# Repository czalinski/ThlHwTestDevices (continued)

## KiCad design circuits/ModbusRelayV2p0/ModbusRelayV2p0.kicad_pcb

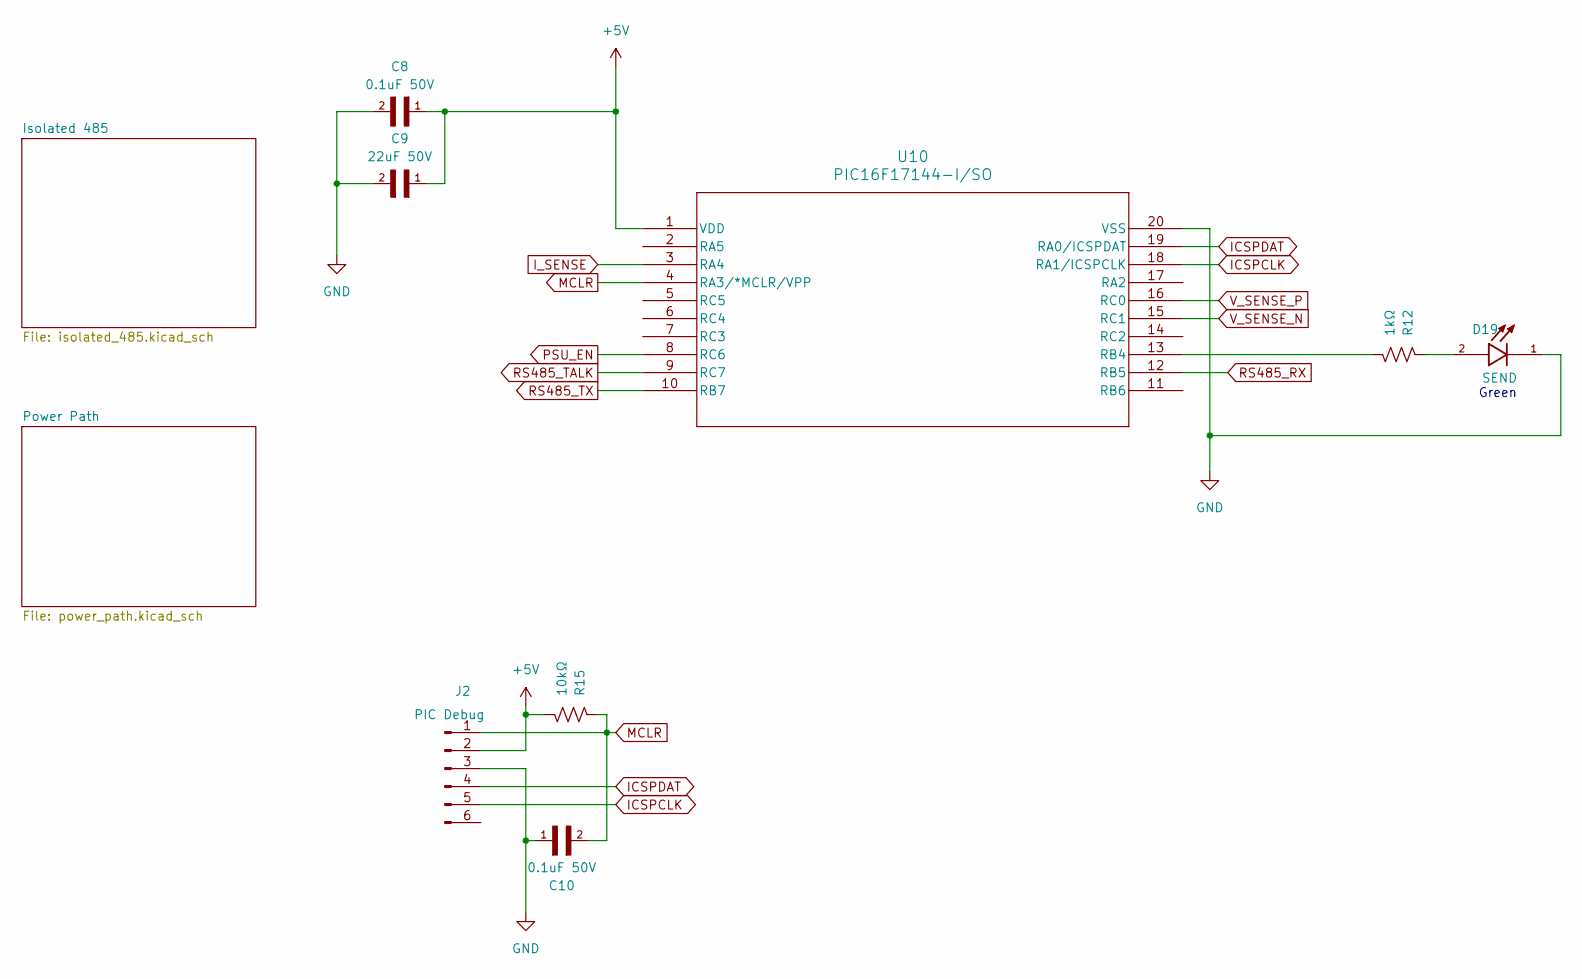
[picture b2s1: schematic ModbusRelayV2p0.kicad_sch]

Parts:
C8, C10: 0.1uF 50V; CAPC2012X70
C9: 22uF 50V; CAPC3216X180N
D19: SEND; LED_LTST-C170GKT; PARTREV I
J2: PIC Debug; PinHeader_1x06_P2.54mm_Horizontal
R12: 1kΩ; RES_1206
R15: 10kΩ; RES_1206
U10: PIC16F17144-I/SO; SOIC20_SO_MCH

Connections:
+5V: C8.1, C9.1, J2.2, R15.2, U10.1 (VDD); also elsewhere on the board
GND: C8.2, C9.2, C10.1, D19.1, J2.3, U10.20 (VSS); also elsewhere on the board
ICSPCLK: J2.5, U10.18 (RA1/ICSPCLK)
ICSPDAT: J2.4, U10.19 (RA0/ICSPDAT)
I_SENSE: U10.3 (RA4); also elsewhere on the board
MCLR: C10.2, J2.1, R15.1, U10.4 (RA3/*MCLR/VPP)
unnamed: D19.2, R12.1
unnamed: R12.2, U10.13 (RB4)
PSU_EN: U10.8 (RC6); also elsewhere on the board
RS485_RX: U10.12 (RB5); also elsewhere on the board
RS485_TALK: U10.9 (RC7); also elsewhere on the board
RS485_TX: U10.10 (RB7); also elsewhere on the board
V_SENSE_N: U10.15 (RC1); also elsewhere on the board
V_SENSE_P: U10.16 (RC0); also elsewhere on the board

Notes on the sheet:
Green

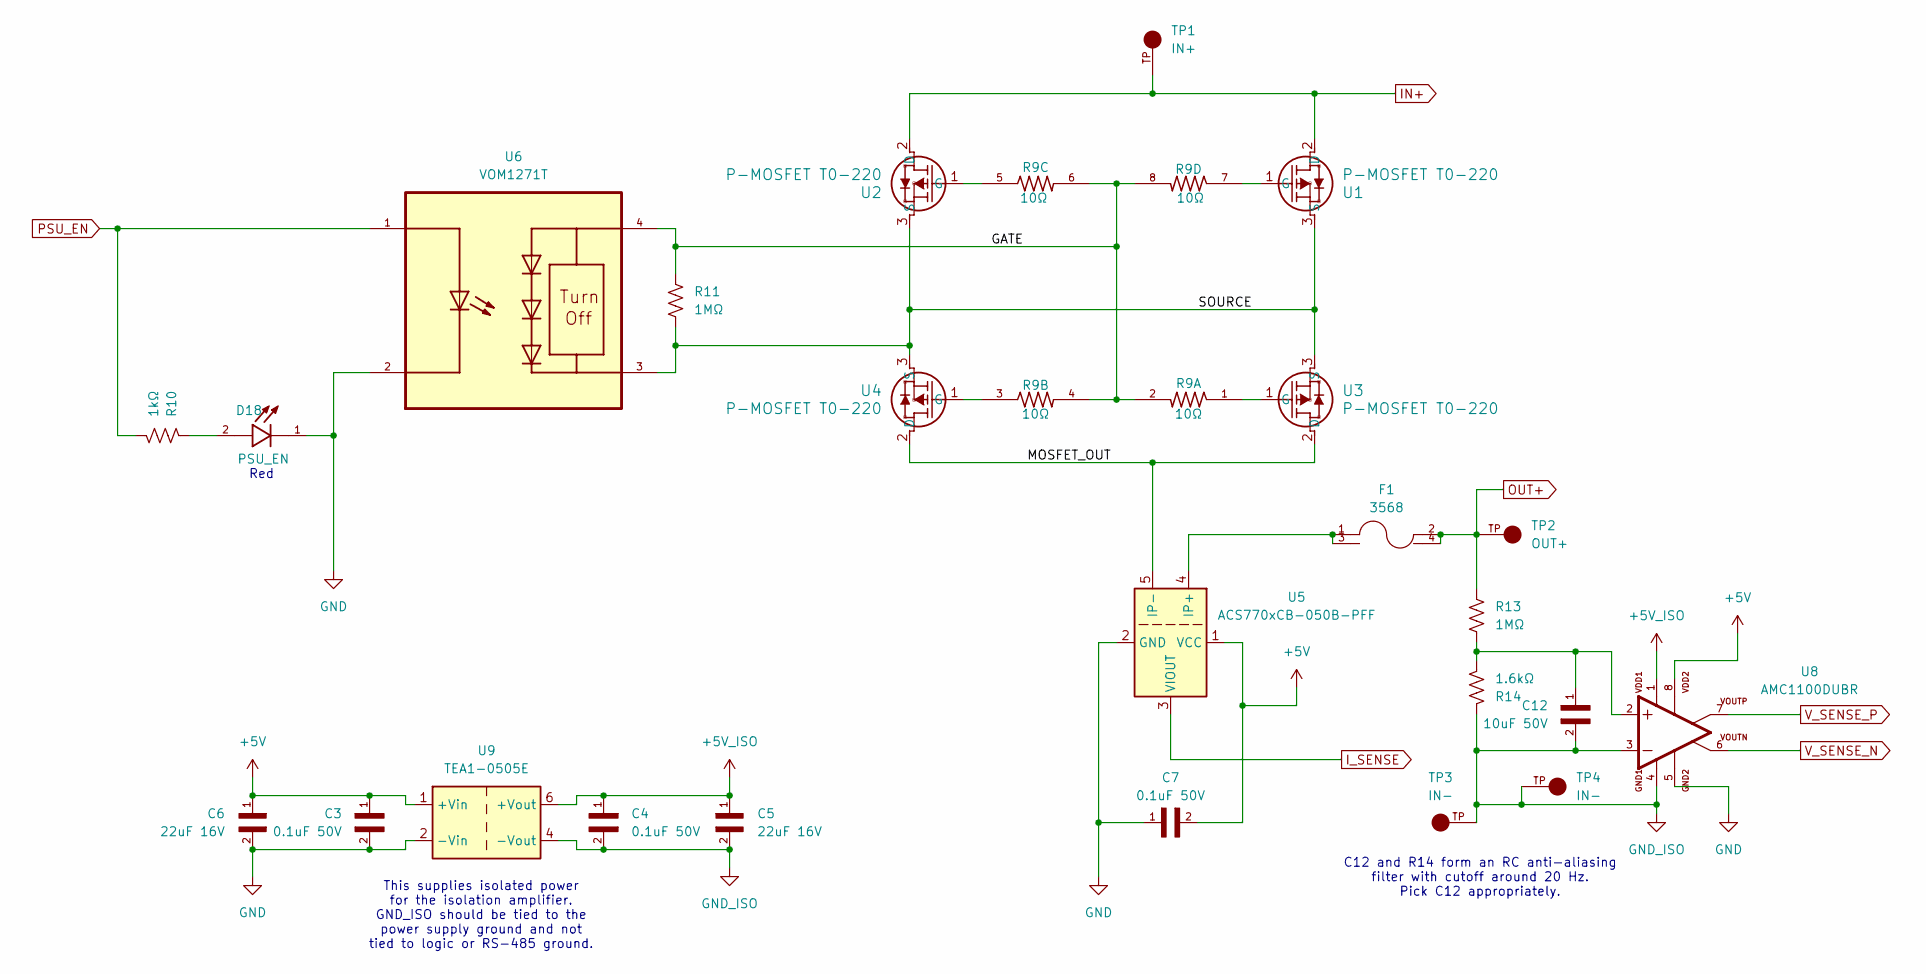
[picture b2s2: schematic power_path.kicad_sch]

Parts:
C3, C4, C7: 0.1uF 50V; CAPC2012X70
C5, C6: 22uF 16V; CAPC3216X95N
C12: 10uF 50V; CAPC3216X180N
D18: PSU_EN; LED_LTST-C170GKT; PARTREV I
F1: 3568; FUSE_3568; PARTREV C
R9: 10Ω; RESCAV80P320X160X70-8N
R10: 1kΩ; RES_1206
R11, R13: 1MΩ; RES_1206
R14: 1.6kΩ; RES_1206
TP1: IN+; KEYSTONE_4954_Slot; PARTREV B; DigiKey_Part_Number 36-4954-ND
TP2: OUT+; KEYSTONE_4954_Slot; PARTREV B; DigiKey_Part_Number 36-4954-ND
TP3, TP4: IN-; KEYSTONE_4954_Slot; PARTREV B; DigiKey_Part_Number 36-4954-ND
U1, U2, U3, U4: P-MOSFET T0-220; TO220AB_VIS
U5: ACS770xCB-050B-PFF; Allegro_CB_PFF
U6: VOM1271T; SOIC254P695X242-4N
U8: AMC1100DUBR; SOP254P1040X485-8N; PARTREV B
U9: TEA1-0505E; Converter_DCDC_TRACO_TEA1-xxxxE_THT

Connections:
+5V: C3.1, C6.1, C7.2, U5.1 (VCC), U8.8, U9.1 (+Vin); also elsewhere on the board
+5V_ISO: C4.1, C5.1, U8.1, U9.6 (+Vout)
/Power Path/GATE: R9.2, R9.4, R9.6, R9.8, R11.1, U6.4
/Power Path/MOSFET_OUT: U3.2 (D), U4.2 (D), U5.5 (IP-)
/Power Path/SOURCE: R11.2, U1.3 (S), U2.3 (S), U3.3 (S), U4.3 (S), U6.3
GND: C3.2, C6.2, C7.1, D18.1, U5.2 (GND), U6.2, U8.5, U9.2 (-Vin); also elsewhere on the board
GND_ISO: C4.2, C5.2, C12.2, R14.1, TP3.TP, TP4.TP, U8.3, U8.4, U9.4 (-Vout)
IN+: TP1.TP, U1.2 (D), U2.2 (D)
I_SENSE: U5.3 (VIOUT); also elsewhere on the board
unnamed: C12.1, R13.2, R14.2, U8.2
unnamed: D18.2, R10.1
unnamed: R9.7, U1.1 (G)
unnamed: R9.5, U2.1 (G)
unnamed: R9.1, U3.1 (G)
unnamed: R9.3, U4.1 (G)
unnamed: F1.1, F1.3, U5.4 (IP+)
OUT+: F1.2, F1.4, R13.1, TP2.TP
PSU_EN: R10.2, U6.1; also elsewhere on the board
V_SENSE_N: U8.6; also elsewhere on the board
V_SENSE_P: U8.7; also elsewhere on the board

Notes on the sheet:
C12 and R14 form an RC anti-aliasing filter with cutoff around 20 Hz. Pick C12 appropriately.
This supplies isolated power for the isolation amplifier. GND_ISO should be tied to the power supply ground and not tied to logic or RS-485 ground.
Red

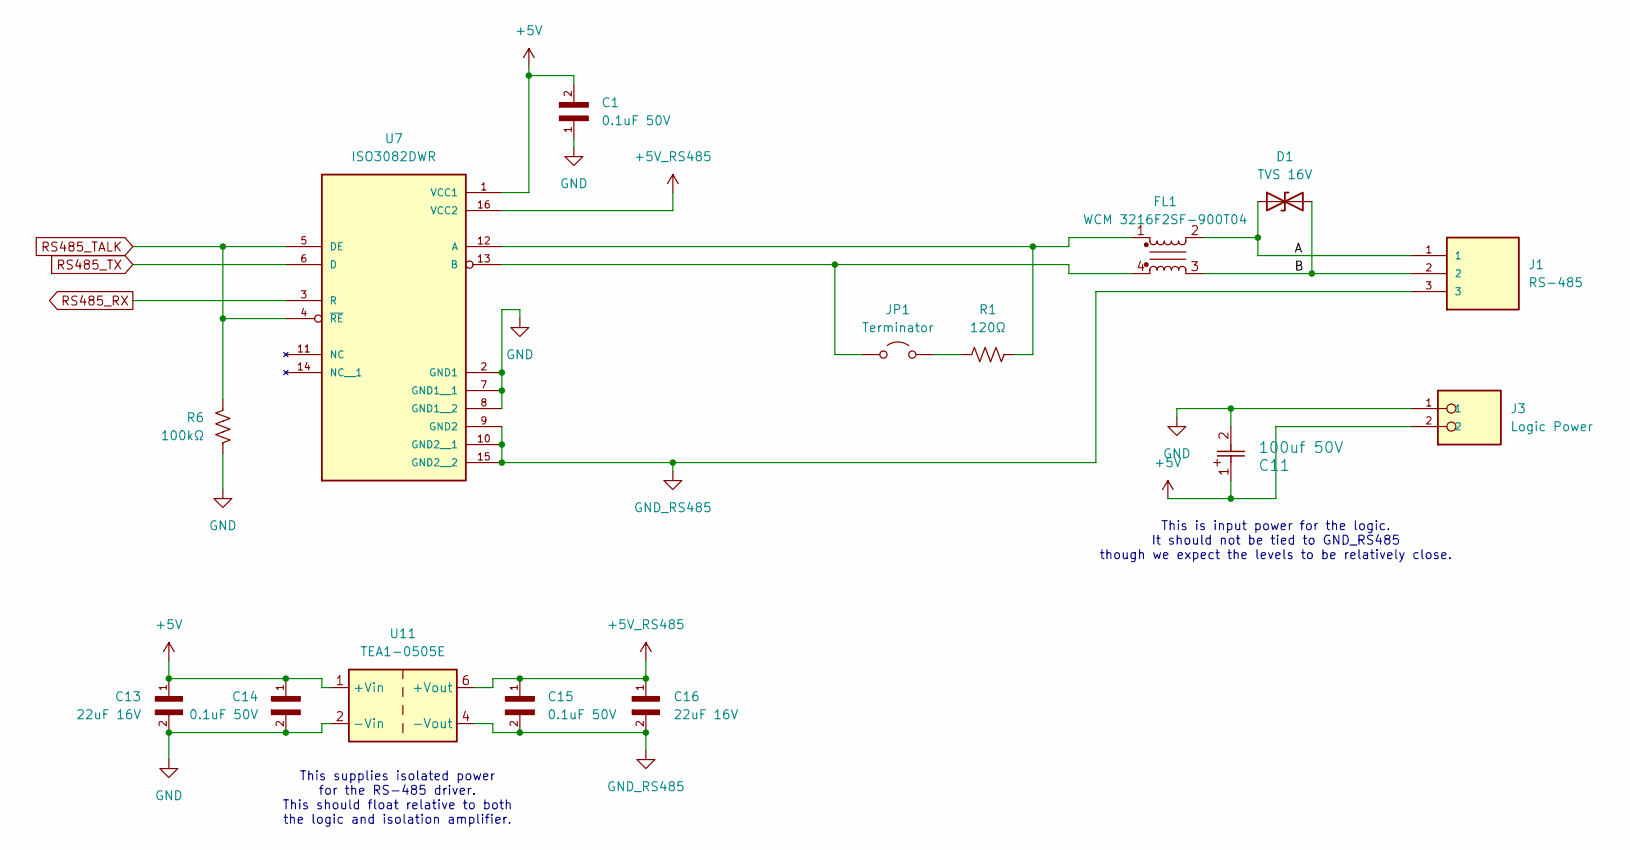
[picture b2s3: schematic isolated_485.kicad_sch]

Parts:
C1, C14, C15: 0.1uF 50V; CAPC2012X70
C11: 100uf 50V; CAP_YX_8X11P5_RUB
C13, C16: 22uF 16V; CAPC3216X95N
D1: TVS 16V; D_SOD-123F
FL1: WCM 3216F2SF-900T04; WCM 3216F2SF-900T04-1206
J1: RS-485; TE_1985205; PARTREV 29.03.2021
J3: Logic Power; PHOENIX_1989748; PARTREV 17.02.2015
JP1: Terminator; PinHeader_1x02_P2.54mm_Vertical
R1: 120Ω; RES_1206
R6: 100kΩ; RES_1206
U7: ISO3082DWR; SOIC127P1030X265-16N; PARTREV J
U11: TEA1-0505E; Converter_DCDC_TRACO_TEA1-xxxxE_THT

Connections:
+5V: C1.2, C11.1, C13.1, C14.1, J3.2, U7.1 (VCC1), U11.1 (+Vin); also elsewhere on the board
+5V_RS485: C15.1, C16.1, U7.16 (VCC2), U11.6 (+Vout)
/Isolated 485/A: D1.1 (A1), FL1.2, J1.1
/Isolated 485/B: D1.2 (A2), FL1.3, J1.2
GND: C1.1, C11.2, C13.2, C14.2, J3.1, R6.2, U7.2 (GND1), U7.7 (GND1__1), U7.8 (GND1__2), U11.2 (-Vin); also elsewhere on the board
GND_RS485: C15.2, C16.2, J1.3, U7.9 (GND2), U7.10 (GND2__1), U7.15 (GND2__2), U11.4 (-Vout)
unnamed: JP1.1 (A), R1.1
unnamed: FL1.4, JP1.2 (B), U7.13 (B)
unnamed: FL1.1, R1.2, U7.12 (A)
RS485_RX: U7.3 (R); also elsewhere on the board
RS485_TALK: R6.1, U7.4 (~RE), U7.5 (DE); also elsewhere on the board
RS485_TX: U7.6 (D); also elsewhere on the board

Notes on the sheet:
This is input power for the logic. It should not be tied to GND_RS485 though we expect the levels to be relatively close.
This supplies isolated power for the RS-485 driver. This should float relative to both the logic and isolation amplifier.

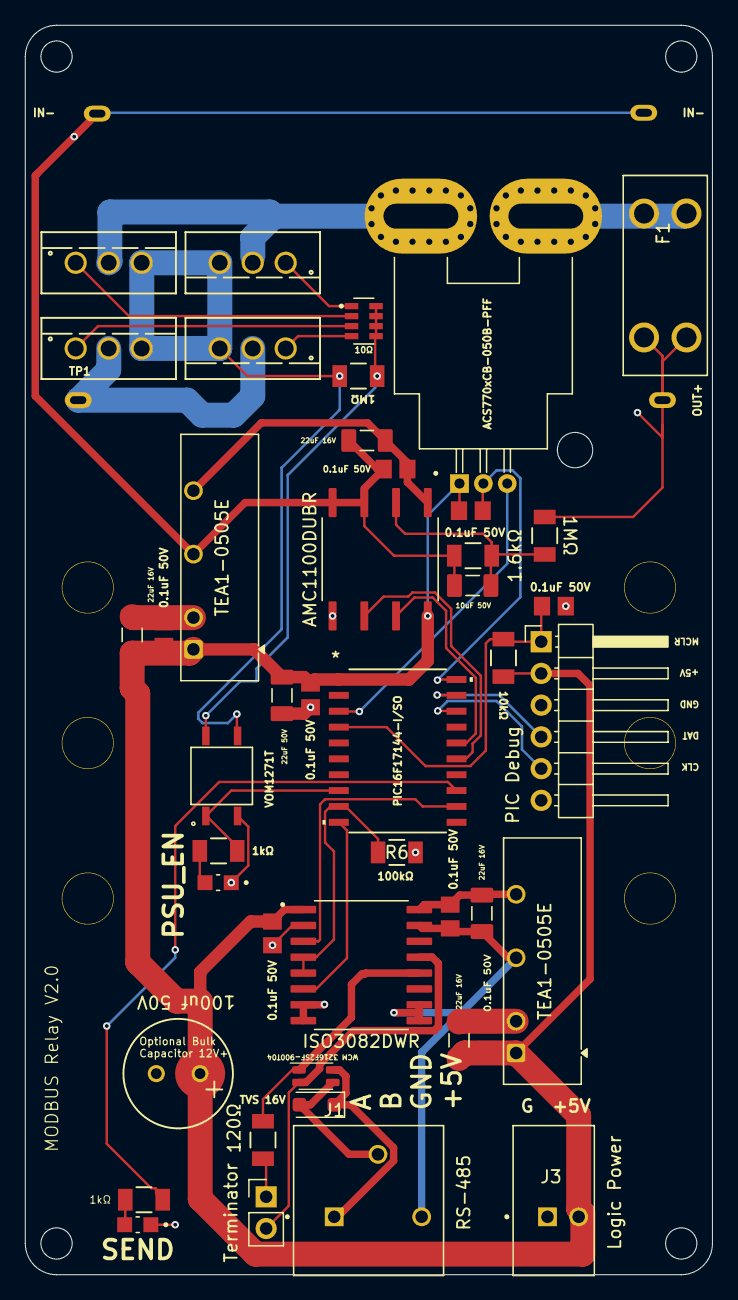
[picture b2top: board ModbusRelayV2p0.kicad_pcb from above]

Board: 2 copper layers, 55.0 x 100.0 mm, 48 parts (0 on the bottom side), 35 nets.

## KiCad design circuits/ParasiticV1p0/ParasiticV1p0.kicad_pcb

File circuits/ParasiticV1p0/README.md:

# Parasitic Logger V1.0

A small logger for the voltage and current of a 12 V automotive battery,
intended for tracking down **parasitic (key-off) current draw** during HASS /
HALT and long-duration vehicle testing. Every 10 seconds it records the battery
voltage and the average current through an external shunt to a CSV file on a
micro-SD card, time-stamped by a DS3231 real-time clock. A serial terminal is
used to set the clock, watch live readings and calibrate.

```
2026-10-03 10:40:00,12.634,42.3
2026-10-03 10:40:10,12.634,41.9
(end-of-interval time, volts, mA)
```

## Hardware

| Ref | Part | Function |
|-----|------|----------|
| U2 | **PIC18F16Q41-I/SO** (see note) | Microcontroller |
| U3 | INA181A1IDBVR | Current-sense amplifier, gain 20 V/V |
| U1 | MSR7805-3.3CW | 12 V to 3.3 V switching regulator |
| J4 | DS3231 RTC module | Real-time clock (I²C) |
| J3 | Micro-SD socket module | Log storage (SPI) |
| J1 | 3-pin | +BATT / shunt sense / GND |
| J2 | 6-pin | PICkit ICSP header |
| J5 | 3-pin | UART terminal (TX / RX / GND), 3.3 V logic |
| — | RAM Meter 20M100A100 | External shunt, 100 A / 100 mV (1 mΩ) |

> **Microcontroller note:** the V1.0 schematic and PCB call for a
> PIC16F17144-I/SO. Its 7 KB of flash is too small for the firmware, so the
> board is built with a **PIC18F16Q41-I/SO** instead: same SOIC-20 footprint
> and identical pin assignment (64 KB flash, 4 KB RAM). The KiCad files have
> not been changed.

### Pin map (PIC18F16Q41)

| Pin | Port | Use |
|-----|------|-----|
| 3 | RA4 | Battery voltage divider (rework, below) |
| 4 | RA3 | MCLR / VPP |
| 6 / 7 | RC4 / RC3 | I²C SDA / SCL to DS3231 |
| 8 / 9 | RC6 / RC7 | UART TX / RX |
| 10–13 | RB7–RB4 | SD card CS / SCK / MOSI / MISO |
| 14 | RC2 | Internal op-amp output (not connected on the PCB) |
| 17 | RA2 | INA181 output (through 1 kΩ / 100 pF) |
| 18 / 19 | RA1 / RA0 | ICSP clock / data |

### Current measurement

The INA181 amplifies the shunt voltage 20× around a VDD/2 reference. In the
microcontroller, op-amp OPA1 adds a further inverting gain of about 14.3 around
an internal DAC also set to VDD/2, and the ADC samples the result against VDD.
Both VDD/2 points are ratiometric, so supply drift cancels; the true VDD is
measured every tick against the internal 2.048 V reference to set the scale.

* Resolution: about 3 mA per ADC count; each record averages about 8,000
  current conversions, so the logged value resolves well below 1 mA.
* Range: about ±5.5 A. Larger currents (cranking, charging) **saturate** —
  intended, since the logger is for parasitic draw.
* Sign: **positive = battery discharging**, negative = charging.

### Required rework on V1.0 boards

1. **Battery voltage divider (not on the PCB).** Hand-wire
   100 kΩ (1 %) from +BATT to RA4 (U2 pin 3), 12 kΩ (1 %) from RA4 to GND,
   and 100 nF from RA4 to GND. This gives a 9.333:1 ratio (full scale ≈ 30 V
   at VDD = 3.3 V) and draws about 0.1 mA from the battery. Other values work;
   set the ratio with `vcal`.
2. **ICSP VDD.** J2 pin 2 (the PICkit VDD sense pin) is not connected to
   +3.3 V; the MCLR 10 kΩ pull-up goes only to J2.2. Add a wire from J2 pin 2
   to +3.3 V. Without it the programmer cannot see target power. (The firmware
   uses an internal pull-up on MCLR, so the board runs either way.)
3. **C3** must be 22 µF, not 22 pF (noted on the schematic).
4. **U2**: fit a PIC18F16Q41-I/SO (see above).

### Wiring to the vehicle

The shunt goes in the battery **negative** lead (low side):

```
 Battery (+) ──[fuse 1 A]──────────────────────── J1.1  +BATT
 Battery (−) ──┬── shunt, battery-side terminal ─ J1.3  GND   (short, thick wire)
               │
             shunt
               │
 Vehicle ground strap ── shunt, load-side terminal ─ J1.2  sense
```

**Keep the J1.3 wire short and heavy.** On V1.0 the INA181's negative input is
the board ground, and the logger's own supply current (≈ 20 mA) returns through
the J1.3 wire. Every milliohm in that wire reads as about 20 mA of false
current. The `zero` calibration removes the steady part of this, which is why
it must be done with the logger wired exactly as it will be used. (V1.1 should
bring the INA181 IN− out on its own Kelvin pin.)

The logger runs from the battery it is measuring but its own current is **not**
included in the reading (it returns on the battery side of the shunt).

## Firmware

Source is in [`firmware/`](firmware/). It is plain C for the
[MPLAB XC8](https://www.microchip.com/en-us/tools-resources/develop/mplab-xc-compilers/xc8)
compiler and uses ChaN's [FatFs](http://elm-chan.org/fsw/ff/) (R0.16, in
`firmware/lib/fatfs`, BSD-style 1-clause license).

### Building

Needs XC8 (v4.00 used) and the Microchip PIC18F-Q device family pack
(1.31.492 used):

```
cd firmware
make                        # -> build/parasitic.hex
make XC8=/path/to/xc8-cc DFP=/path/to/PIC18F-Q_DFP/1.31.492
```

### Programming

MPLAB X dropped PICkit 3 support in v6.25. On Linux the PICkit 3 can be used
with the open-source **pk2cmd** ([jaka-fi/pk2cmd](https://github.com/jaka-fi/pk2cmd)
with the device file from [cjacker/pk2cmd-minus](https://github.com/cjacker/pk2cmd-minus)),
after loading the PICkit 3 "scripting" firmware (PK3OSV023202.hex). With the
board powered from 12 V:

```
make flash                  # pk2cmd -PPIC18F16Q41 -W -R -F build/parasitic.hex -M -Y
```

`-W` tells pk2cmd the board supplies its own power; `-R` releases MCLR
afterwards so the new firmware starts. To return a PICkit 3 to
MPLAB mode, hold its button while plugging it in and connect with MPLAB X ≤ 6.20.

## Using the logger

### SD card

Any micro-SD card formatted **FAT32** (cards up to 32 GB come that way; larger
cards are exFAT and must be reformatted as FAT32). Records go to one file per
day in the root directory, named from the RTC date, e.g. `20261003.CSV`. A new
file starts with a `time,volts,mA` header. Each record is flushed to the card
as it is written, so the card can be removed at any time with at most one
record lost; `log off` first is cleaner. If the card is missing or fails, the
logger retries every 30 s.

At 10 s per record a day is about 310 KB.

### Terminal

Connect a 3.3 V USB-serial adapter to J5 (TX → adapter RX, RX → adapter TX,
GND) at **115200 8N1**, e.g. `picocom -b 115200 /dev/ttyUSB0`.

| Command | Action |
|---------|--------|
| `help` | List commands |
| `time` | Show the RTC time |
| `time 2026-10-03 14:05:00` | Set the RTC (24-hour) |
| `status` | Last reading, supply voltage, log file, free space, calibration |
| `live on` / `live off` | Echo each record to the terminal (default on) |
| `log on` / `log off` | Start / stop SD logging (setting is remembered) |
| `zero` | Current zero calibration (see below) |
| `vcal 12.634` | Battery voltage calibration to a meter reading in volts |
| `ical 1000` | Current gain calibration to a known current in mA |
| `defaults` | Restore default calibration |

Calibration commands take effect at the end of the next 10 s record and are
stored in EEPROM.

### Calibration

1. **Zero (required).** Wire the logger as it will be used, then disconnect the
   vehicle ground strap from the shunt so no current flows. Wait for a record,
   type `zero`, and wait for `cal saved`. Reconnect.
2. **Voltage.** Measure the battery with a good meter and enter `vcal <volts>`.
3. **Current gain (optional).** With a known steady load (e.g. 1.000 A from a
   bench supply through the shunt) enter `ical <mA>`. The default assumes the
   nominal 1 mΩ shunt and amplifier gains, typically within a few percent.

## Status

* Firmware written and compiled (25 KB of 64 KB flash, 1.2 KB of 4 KB RAM).
* **Not yet tested on hardware**, and pk2cmd programming of the PIC18F16Q41
  with a PICkit 3 is not yet confirmed.

## Changes wanted for V1.1

* Change U2 to PIC18F16Q41-I/SO in the schematic and BOM.
* Add the battery voltage divider and filter capacitor to RA4.
* Connect J2 pin 2 to +3.3 V.
* Bring INA181 IN− out on a separate J1 pin (4-pin connector) for Kelvin
  sensing at the shunt.
* Fix the DS3231 symbol pin names (pin graphics are right; names were copied
  from the SD-card symbol).
* C3 = 22 µF.

## License

The design files, firmware and documentation are released under the
[MIT License](../../LICENSE). The bundled FatFs library in
`firmware/lib/fatfs` keeps its own BSD-style license
([LICENSE.txt](firmware/lib/fatfs/LICENSE.txt)).

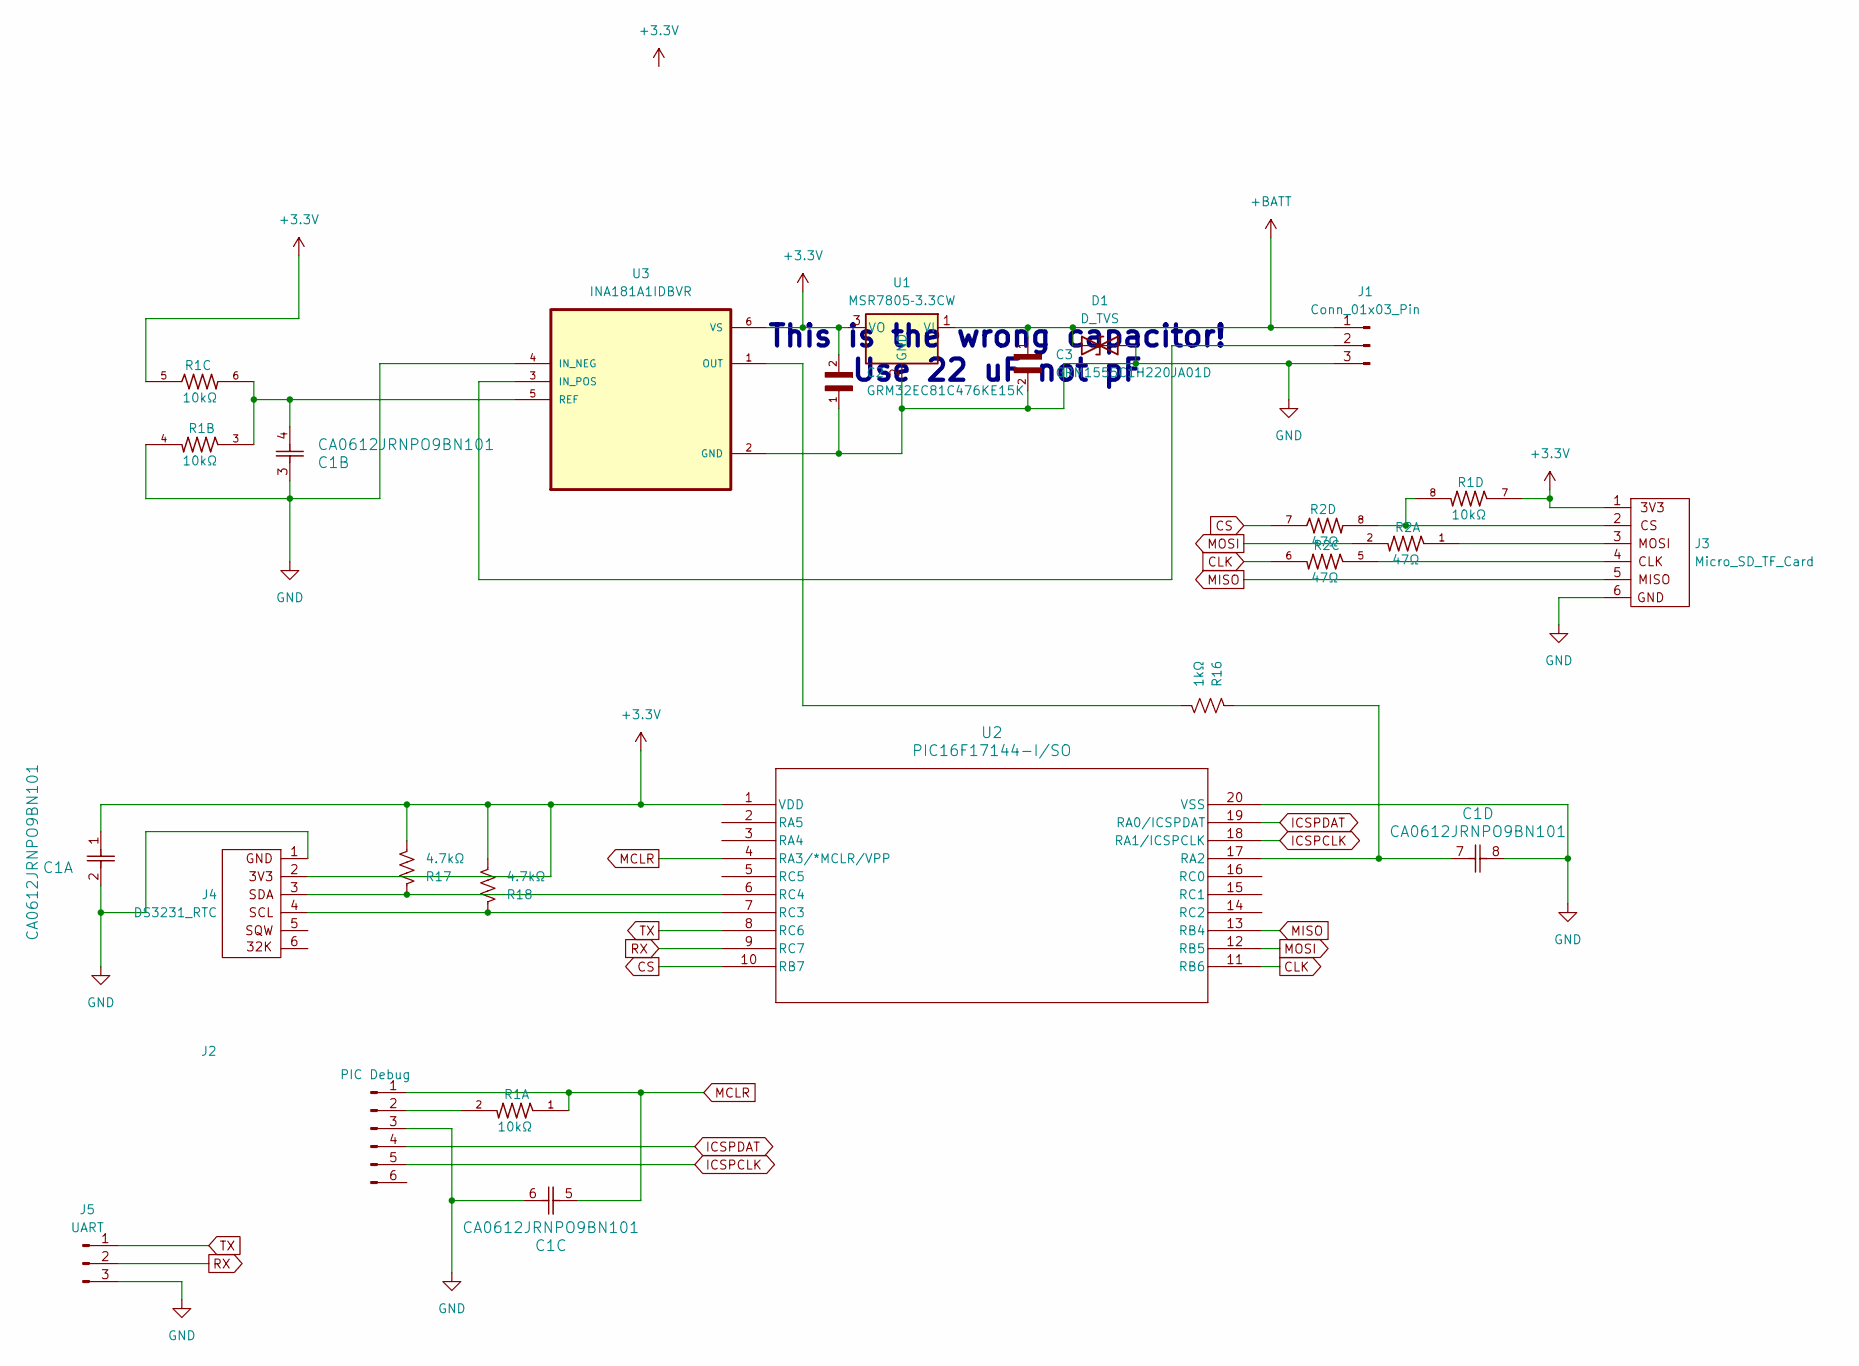
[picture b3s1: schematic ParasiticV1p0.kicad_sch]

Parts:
C1: CA0612JRNPO9BN101; CAP_CA0612_3P2X1P6_YAG
C2: GRM32EC81C476KE15K; CAPC3225X270N
C3: GRM1555C1H220JA01D; CAPC1005X55N
D1: D_TVS; D_SMC_Handsoldering
J1: Conn_01x03_Pin; PinHeader_1x03_P2.54mm_Vertical
J2: PIC Debug; PinHeader_1x06_P2.54mm_Horizontal
J3: Micro_SD_TF_Card
J4: DS3231_RTC; PinHeader_1x06_P2.54mm_Vertical
J5: UART; PinHeader_1x03_P2.54mm_Vertical
R1: 10kΩ; RESCAV80P320X160X70-8N
R2: 47Ω; RESCAV80P320X160X70-8N
R16: 1kΩ; RES_1206
R17, R18: 4.7kΩ; RES_1206
U1: MSR7805‑3.3CW; 3-SIP
U2: PIC16F17144-I/SO; SOIC20_SO_MCH
U3: INA181A1IDBVR; SOT95P280X145-6N

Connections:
+3.3V: C1.1, C2.2, J3.1 (3V3), J4.2 (CS), R1.5, R1.7, R17.2, R18.2, U1.3 (VO), U2.1 (VDD), U3.6 (VS)
+BATT: C3.1, D1.1 (A1), J1.1, U1.1 (VI)
CLK: R2.6, U2.11 (RB6)
CS: R2.7, U2.10 (RB7)
GND: C1.2, C1.3, C1.6, C1.8, C2.1, C3.2, D1.2 (A2), J1.3, J2.3, J3.6 (GND), J4.1 (3V3), J5.3, R1.4, U1.2 (GND), U2.20 (VSS), U3.2 (GND), U3.4 (IN_NEG)
ICSPCLK: J2.5, U2.18 (RA1/ICSPCLK)
ICSPDAT: J2.4, U2.19 (RA0/ICSPDAT)
MCLR: C1.5, J2.1, R1.1, U2.4 (RA3/*MCLR/VPP)
MISO: J3.5 (MISO), U2.13 (RB4)
MOSI: R2.2, U2.12 (RB5)
unnamed: J1.2, U3.3 (IN_POS)
unnamed: J2.2, R1.2
unnamed: J3.4 (CLK), R2.5
unnamed: J3.2 (CS), R1.8, R2.8
unnamed: J3.3 (MOSI), R2.1
unnamed: J4.4 (CLK), R18.1, U2.7 (RC3)
unnamed: J4.3 (MOSI), R17.1, U2.6 (RC4)
unnamed: C1.7, R16.1, U2.17 (RA2)
unnamed: R16.2, U3.1 (OUT)
unnamed: C1.4, R1.3, R1.6, U3.5 (REF)
RX: J5.2, U2.9 (RC7)
TX: J5.1, U2.8 (RC6)

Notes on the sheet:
This is the wrong capacitor! Use 22 uF not pF

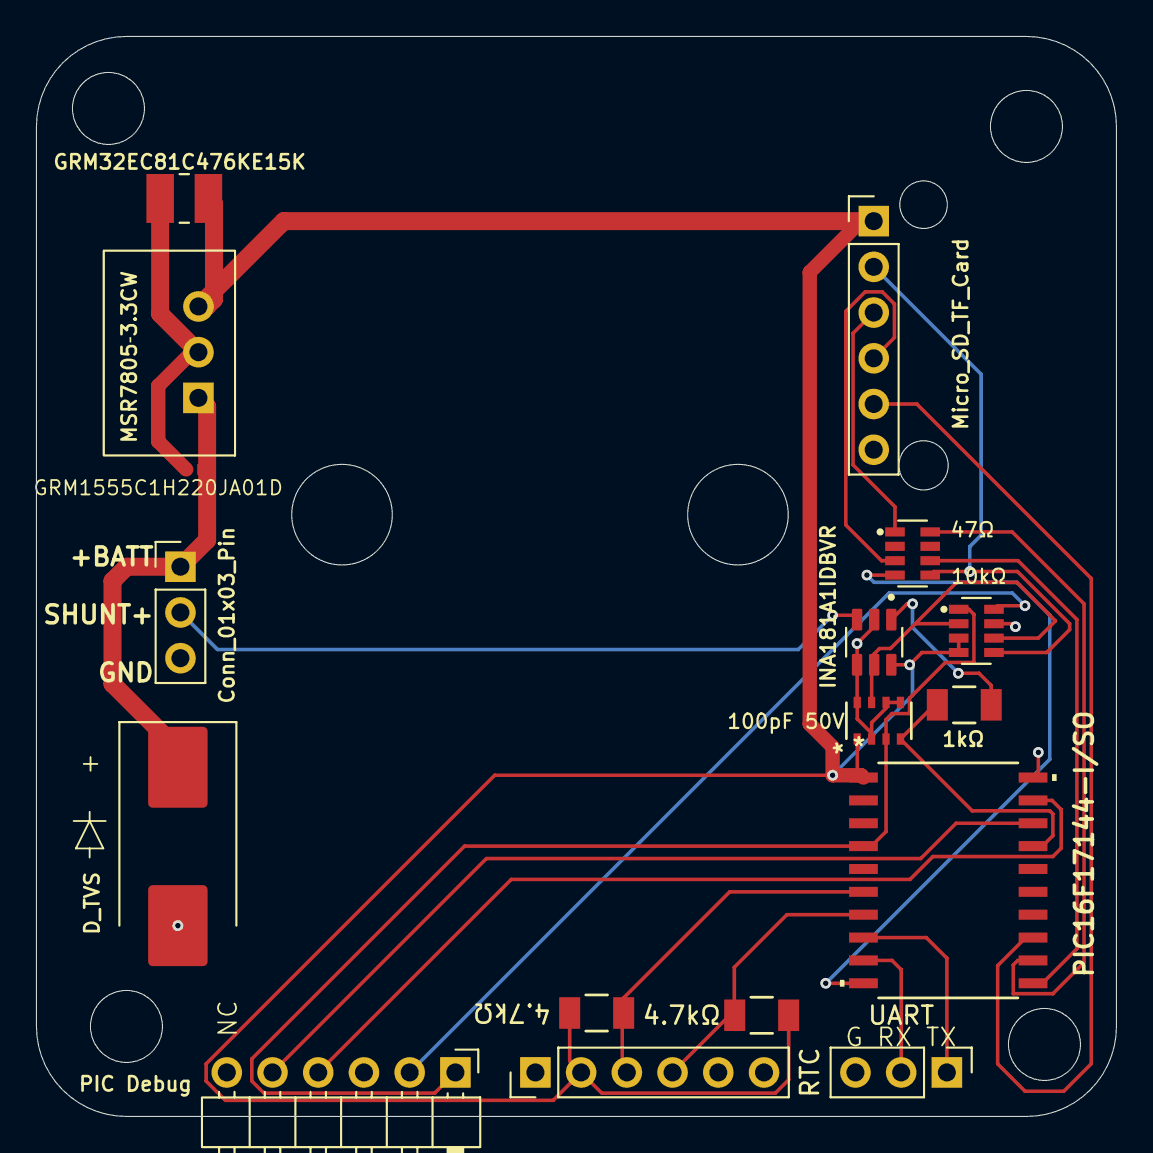
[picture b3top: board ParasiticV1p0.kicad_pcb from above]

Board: 2 copper layers, 60.0 x 60.0 mm, 17 parts (0 on the bottom side), 22 nets.

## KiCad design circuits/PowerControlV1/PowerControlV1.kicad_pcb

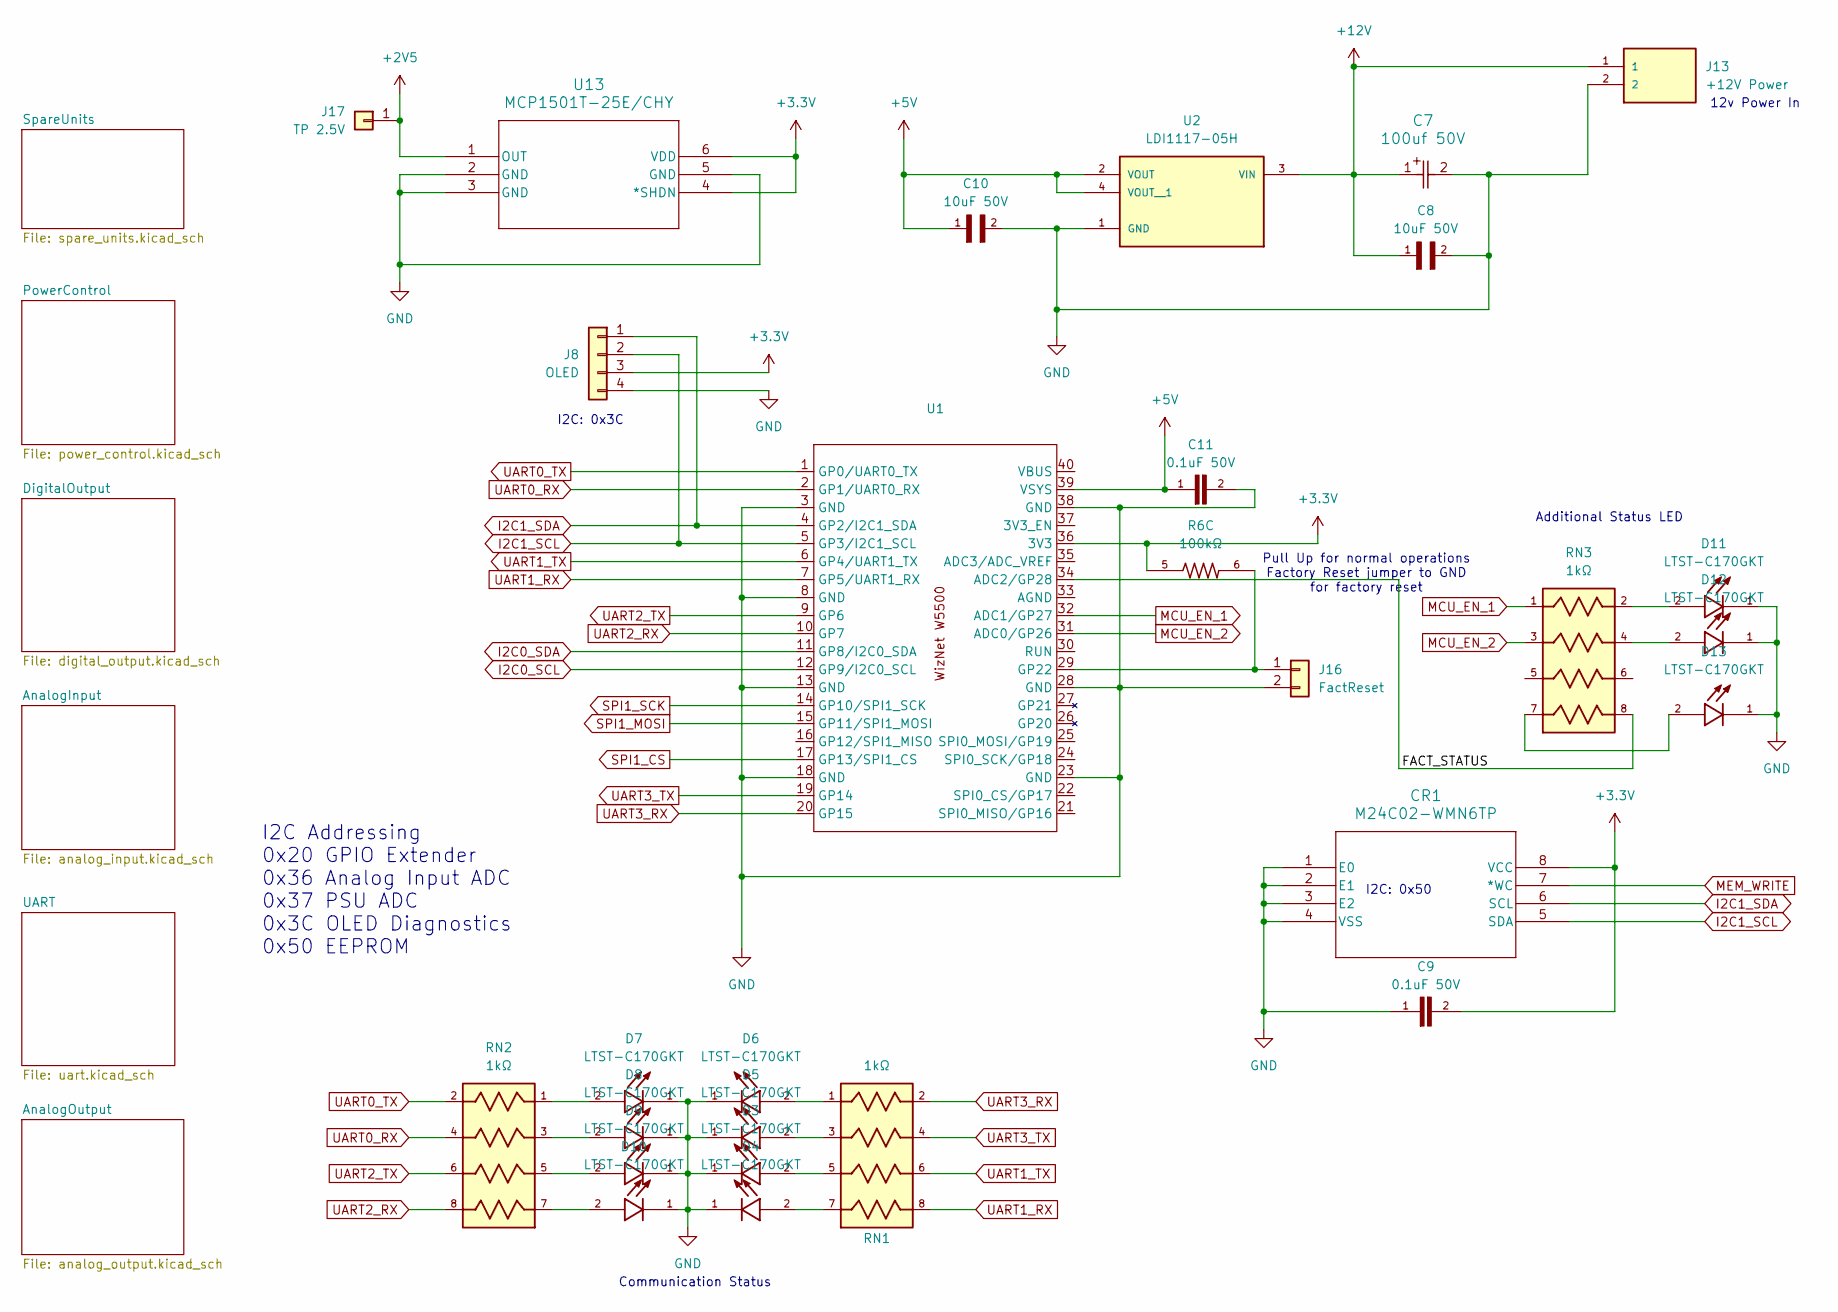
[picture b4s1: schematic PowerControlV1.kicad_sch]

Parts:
C7: 100uf 50V; CAP_YX_8X11P5_RUB
C8, C10: 10uF 50V; CAPC3216X180N
C9, C11: 0.1uF 50V; CAPC2012X70
CR1: M24C02-WMN6TP; SO-8_STM
D3, D4, D5, D6, D7, D8, D9, D10, D11, D12, D13: LTST-C170GKT; LED_LTST-C170GKT; PARTREV I
J8: OLED; PinHeader_1x04_P2.54mm_Vertical
J13: +12V Power; CUI_TB005-762-02BE
J16: FactReset; PinHeader_1x02_P2.54mm_Vertical
J17: TP 2.5V; PinHeader_1x01_P2.54mm_Vertical
R6: 100kΩ; RESCAV80P320X160X70-8N
RN1, RN2, RN3: 1kΩ; RESCAXS50P200X100X55-8N
U1: WizNetPico_Elevated
U2: LDI1117-05H; SOT230P700X165-4N; PARTREV 2023-02-01
U13: MCP1501T-25E/CHY; SOT-23_OT&slash_OTY_MCH

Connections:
+2V5: J17.1, U13.1 (OUT); also elsewhere on the board
+3.3V: C9.2, CR1.8 (VCC), J8.3, R6.5, U1.36 (3V3), U13.4 (*SHDN), U13.6 (VDD); also elsewhere on the board
+5V: C10.1, C11.1, U1.39 (VSYS), U2.2 (VOUT), U2.4 (VOUT__1); also elsewhere on the board
+12V: C7.1, C8.1, J13.1, U2.3 (VIN); also elsewhere on the board
/FACT_STATUS: RN3.8, U1.34 (ADC2/GP28)
GND: C7.2, C8.2, C9.1, C10.2, C11.2, CR1.1 (E0), CR1.2 (E1), CR1.3 (E2), CR1.4 (VSS), D3.1, D4.1, D5.1, D6.1, D7.1, D8.1, D9.1, D10.1, D11.1, D12.1, D13.1, J8.4, J13.2, J16.2, U1.3 (GND), U1.8 (GND), U1.13 (GND), U1.18 (GND), U1.23 (GND), U1.28 (GND), U1.38 (GND), U2.1 (GND), U13.2 (GND), U13.3 (GND), U13.5 (GND); also elsewhere on the board
I2C0_SCL: U1.12 (GP9/I2C0_SCL); also elsewhere on the board
I2C0_SDA: U1.11 (GP8/I2C0_SDA); also elsewhere on the board
I2C1_SCL: CR1.5 (SDA), J8.2, U1.5 (GP3/I2C1_SCL); also elsewhere on the board
I2C1_SDA: CR1.6 (SCL), J8.1, U1.4 (GP2/I2C1_SDA); also elsewhere on the board
MCU_EN_1: RN3.1, U1.32 (ADC1/GP27); also elsewhere on the board
MCU_EN_2: RN3.3, U1.31 (ADC0/GP26); also elsewhere on the board
MEM_WRITE: CR1.7 (*WC)
unnamed: D3.2, RN1.5
unnamed: D4.2, RN1.7
unnamed: D5.2, RN1.3
unnamed: D6.2, RN1.1
unnamed: D7.2, RN2.1
unnamed: D8.2, RN2.3
unnamed: D9.2, RN2.5
unnamed: D10.2, RN2.7
unnamed: D11.2, RN3.2
unnamed: D12.2, RN3.4
unnamed: D13.2, RN3.7
unnamed: J16.1, R6.6, U1.29 (GP22)
SPI1_CS: U1.17 (GP13/SPI1_CS); also elsewhere on the board
SPI1_MOSI: U1.15 (GP11/SPI1_MOSI); also elsewhere on the board
SPI1_SCK: U1.14 (GP10/SPI1_SCK); also elsewhere on the board
UART0_RX: RN2.4, U1.2 (GP1/UART0_RX); also elsewhere on the board
UART0_TX: RN2.2, U1.1 (GP0/UART0_TX); also elsewhere on the board
UART1_RX: RN1.8, U1.7 (GP5/UART1_RX); also elsewhere on the board
UART1_TX: RN1.6, U1.6 (GP4/UART1_TX); also elsewhere on the board
UART2_RX: RN2.8, U1.10 (GP7); also elsewhere on the board
UART2_TX: RN2.6, U1.9 (GP6); also elsewhere on the board
UART3_RX: RN1.2, U1.20 (GP15); also elsewhere on the board
UART3_TX: RN1.4, U1.19 (GP14); also elsewhere on the board

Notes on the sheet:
Pull Up for normal operations Factory Reset jumper to GND for factory reset
I2C: 0x3C
Additional Status LED
I2C Addressing 0x20 GPIO Extender 0x36 Analog Input ADC 0x37 PSU ADC 0x3C OLED Diagnostics 0x50 EEPROM
12v Power In
Communication Status
I2C: 0x50
